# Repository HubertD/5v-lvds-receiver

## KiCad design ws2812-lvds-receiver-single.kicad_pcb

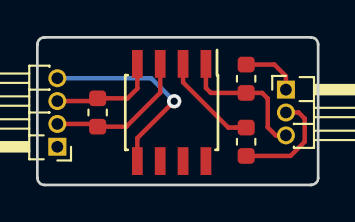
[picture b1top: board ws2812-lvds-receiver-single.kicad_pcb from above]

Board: 2 copper layers, 15.6 x 8.2 mm, 6 parts (0 on the bottom side), 6 nets.

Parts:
C1: 1uF; C_0603_1608Metric
J1: Conn_01x04_Female; PinHeader_1x04_P1.27mm_Horizontal
J2: Conn_01x03_Female; PinHeader_1x03_P1.27mm_Horizontal
R1, R2: 100R; R_0603_1608Metric
U1: DS90C402; SOIC-8_3.9x4.9mm_P1.27mm

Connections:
+5V: C1.1, J1.1, J2.3, U1.1
GND: C1.2, J1.4, J2.1, U1.5
unnamed: J1.2, R1.1, U1.3
unnamed: J1.3, R1.2, U1.4
unnamed: J2.2, R2.1
unnamed: R2.2, U1.2

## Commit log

2018-06-24 initial checkin
2018-06-24 add gerbers
